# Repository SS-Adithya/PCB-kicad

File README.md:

# PCB-kicad

This is a repositary made to put all my Kicad works and there will be some good projects done here.

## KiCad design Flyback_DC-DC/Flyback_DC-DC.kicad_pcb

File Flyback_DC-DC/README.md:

This a PCB design for a 5V DC-DC Flyback converter that is not exacty the most optimised but on a working level.

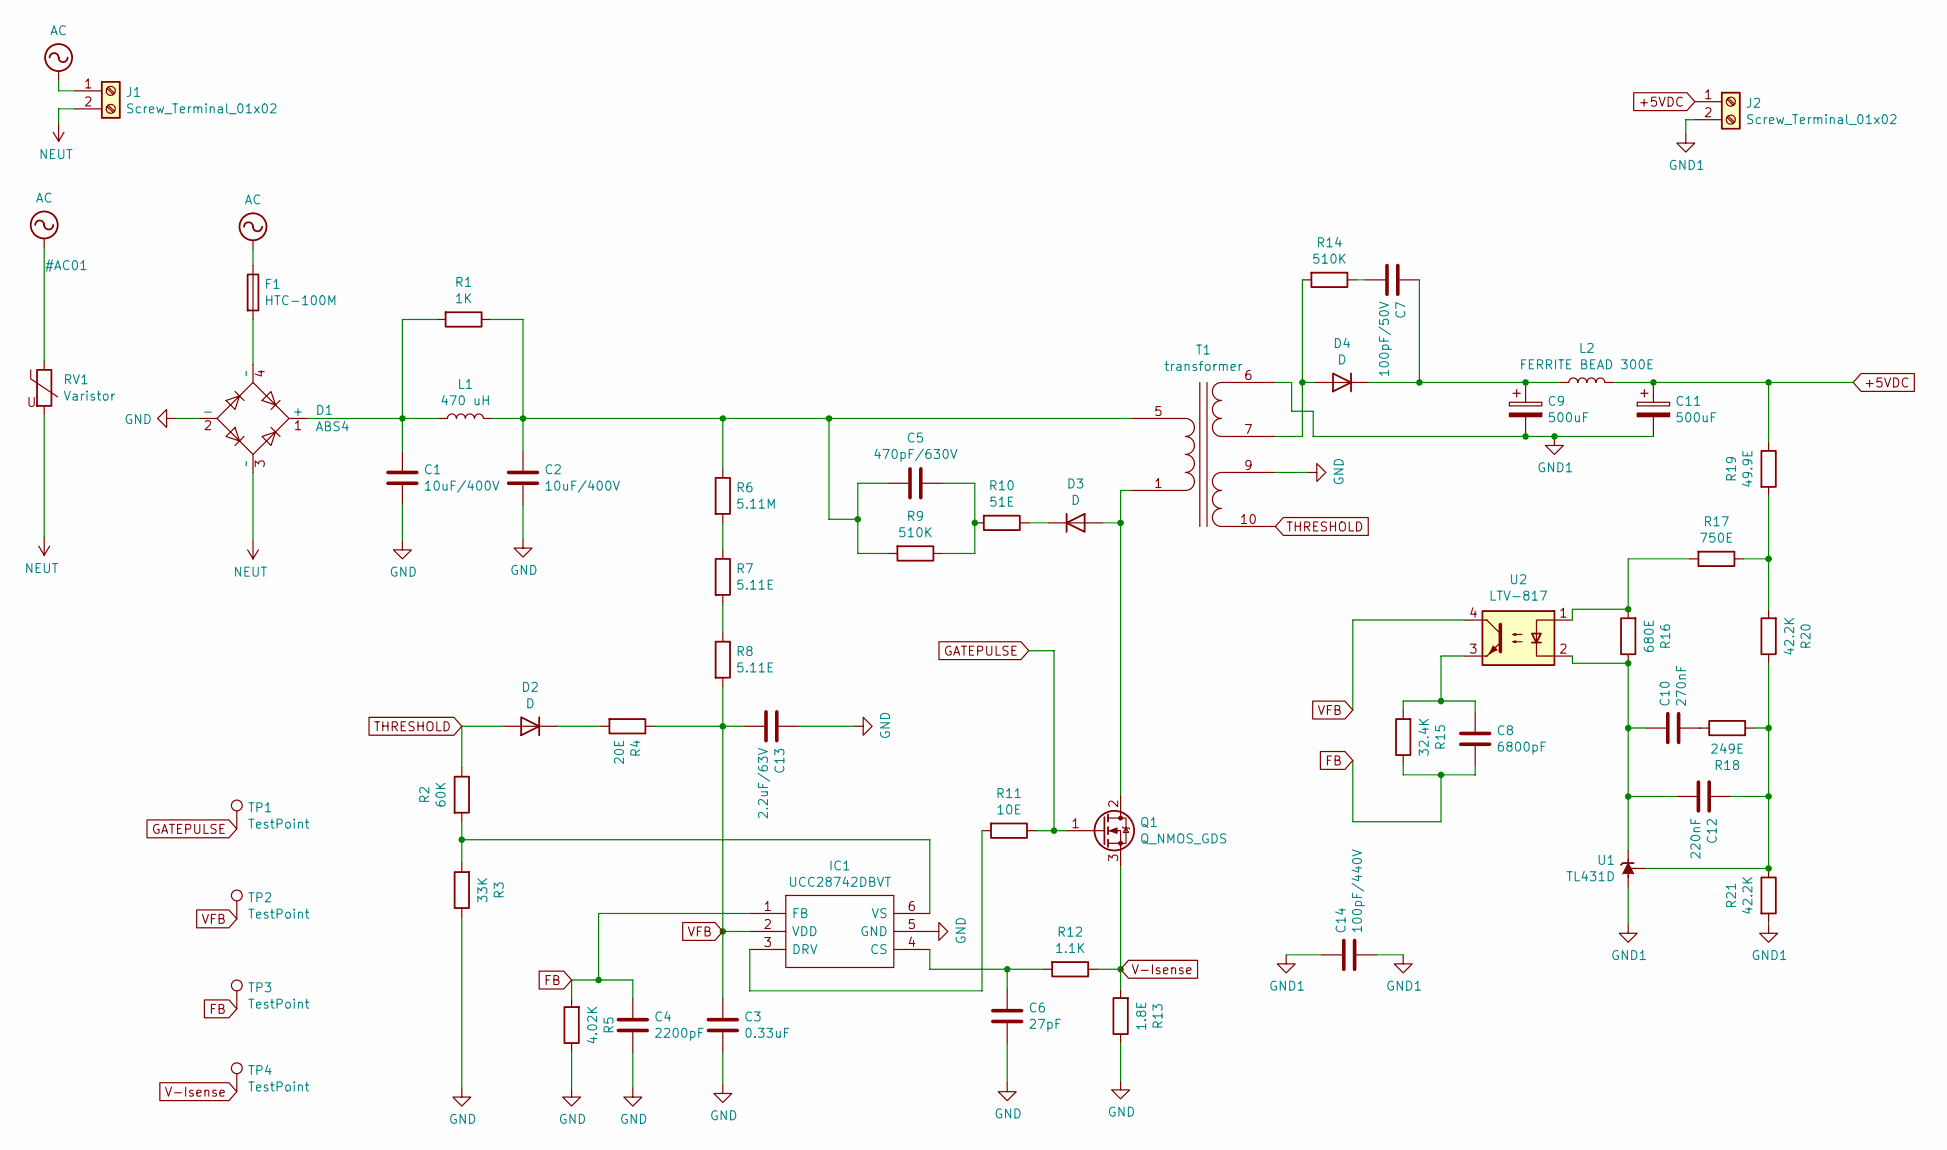
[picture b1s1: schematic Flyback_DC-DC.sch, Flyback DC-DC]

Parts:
C1, C2: 10uF/400V; CP_Radial_D10.0mm_P5.00mm
C3: 0.33uF; C_0805_2012Metric_Pad1.18x1.45mm_HandSolder
C4: 2200pF; C_0805_2012Metric_Pad1.18x1.45mm_HandSolder
C5: 470pF/630V; C_1206_3216Metric
C6: 27pF; C_0805_2012Metric_Pad1.18x1.45mm_HandSolder
C7: 100pF/50V; C_0201_0603Metric_Pad0.64x0.40mm_HandSolder
C8: 6800pF; C_0805_2012Metric_Pad1.18x1.45mm_HandSolder
C9, C11: 500uF; CP_Radial_D8.0mm_P3.50mm
C10: 270nF; C_0805_2012Metric_Pad1.18x1.45mm_HandSolder
C12: 220nF; C_0805_2012Metric_Pad1.18x1.45mm_HandSolder
C13: 2.2uF/63V; CP_Radial_D8.0mm_P3.50mm
C14: 100pF/440V; C_Disc_D10.5mm_W5.0mm_P7.50mm
D1: ABS4; Diode_Bridge_Diotec_ABS
D2, D3, D4: D; D_1206_3216Metric_Castellated
F1: HTC-100M; HTC100M
IC1: UCC28742DBVT; SOT95P280X145-6N; Manufacturer_Part_Number UCC28742DBVT; Mouser Part Number 595-UCC28742DBVT
J1: Screw_Terminal_01x02; TerminalBlock_bornier-3_P5.08mm
J2: Screw_Terminal_01x02; TerminalBlock_bornier-2_P5.08mm
L1: 470 uH; RLB0914
L2: FERRITE BEAD 300E; L_0805_2012Metric_Pad1.05x1.20mm_HandSolder
Q1: Q_NMOS_GDS; TO-252-2
R1: 1K; R_0805_2012Metric_Pad1.20x1.40mm_HandSolder
R2: 60K; R_0805_2012Metric_Pad1.20x1.40mm_HandSolder
R3: 33K; R_0805_2012Metric_Pad1.20x1.40mm_HandSolder
R4: 20E; R_0805_2012Metric_Pad1.20x1.40mm_HandSolder
R5: 4.02K; R_0805_2012Metric_Pad1.20x1.40mm_HandSolder
R6: 5.11M; R_1206_3216Metric
R7, R8: 5.11E; R_1206_3216Metric
R9, R14: 510K; R_0805_2012Metric_Pad1.20x1.40mm_HandSolder
R10: 51E; R_0805_2012Metric_Pad1.20x1.40mm_HandSolder
R11: 10E; R_0805_2012Metric_Pad1.20x1.40mm_HandSolder
R12: 1.1K; R_0805_2012Metric_Pad1.20x1.40mm_HandSolder
R13: 1.8E; R_0805_2012Metric_Pad1.20x1.40mm_HandSolder
R15: 32.4K; R_0805_2012Metric_Pad1.20x1.40mm_HandSolder
R16: 680E; R_0805_2012Metric_Pad1.20x1.40mm_HandSolder
R17: 750E; R_0805_2012Metric_Pad1.20x1.40mm_HandSolder
R18: 249E; R_0805_2012Metric_Pad1.20x1.40mm_HandSolder
R19: 49.9E; R_0805_2012Metric_Pad1.20x1.40mm_HandSolder
R20, R21: 42.2K; R_0805_2012Metric_Pad1.20x1.40mm_HandSolder
RV1: Varistor; MOV14D431KTR
T1: transformer; Transformer_CHK_EI42-5VA_2xSec
TP1, TP2, TP3, TP4: TestPoint; PinHeader_1x01_P2.54mm_Vertical
U1: TL431D; SOIC-8_3.9x4.9mm_P1.27mm
U2: LTV-817; DIP-4_W7.62mm

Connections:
+5VDC: C11.1, J2.1, L2.2, R19.1
AC: F1.1, J1.1, RV1.1
FB: C4.1, C8.2, IC1.1 (FB), R5.2, R15.1, TP3.1
GATEPULSE: Q1.1 (G), R11.1, TP1.1
GND: C1.2, C2.2, C3.2, C4.2, C6.2, C13.1, D1.2 (-), IC1.5 (GND), R3.1, R5.1, R13.1, T1.9 (SC)
GND1: C9.2, C11.2, C14.1, C14.2, J2.2, R21.2, T1.6 (SA), U1.2 (A), U1.3 (A), U1.6 (A), U1.7 (A)
NEUT: D1.3 (~~), J1.2, RV1.2
unnamed: C1.1, D1.1 (+), L1.1, R1.2
unnamed: C2.1, C5.2, L1.2, R1.1, R6.1, R9.2, T1.5 (AA)
unnamed: C5.1, R9.1, R10.2
unnamed: C6.1, IC1.4 (CS), R12.2
unnamed: C7.1, C9.1, D4.1 (K), L2.1
unnamed: C7.2, R14.1
unnamed: C8.1, R15.2, U2.3
unnamed: C10.1, C12.2, R16.1, U1.1 (K), U2.2
unnamed: C10.2, R18.1
unnamed: C12.1, R18.2, R20.1, R21.1, U1.8 (REF)
unnamed: D1.4 (~~), F1.2
unnamed: D2.1 (K), R4.2
unnamed: D3.1 (K), R10.1
unnamed: D3.2 (A), Q1.2 (D), T1.1 (AB)
unnamed: D4.2 (A), R14.2, T1.7 (SB)
unnamed: IC1.3 (DRV), R11.2
unnamed: IC1.6 (VS), R2.2, R3.2
unnamed: R6.2, R7.1
unnamed: R7.2, R8.1
unnamed: R16.2, R17.2, U2.1
unnamed: R17.1, R19.2, R20.2
THRESHOLD: D2.2 (A), R2.1, T1.10 (SD)
V-Isense: Q1.3 (S), R12.1, R13.2, TP4.1
VFB: C3.1, C13.2, IC1.2 (VDD), R4.1, R8.2, TP2.1, U2.4

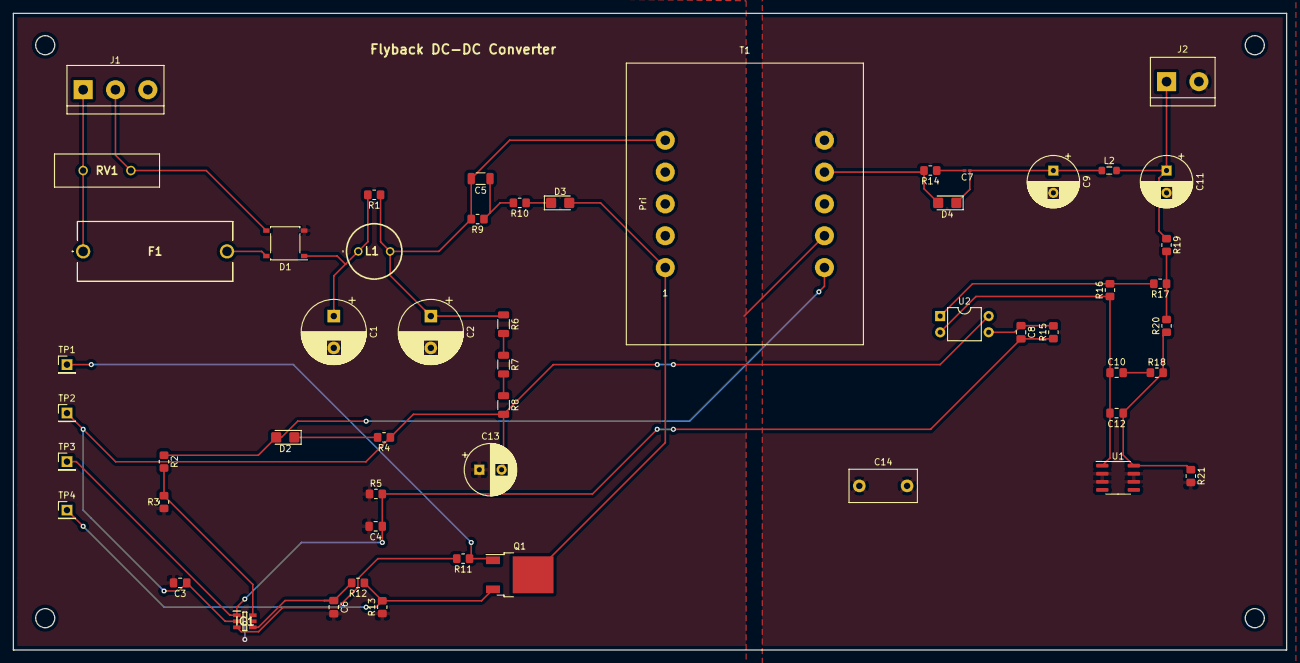
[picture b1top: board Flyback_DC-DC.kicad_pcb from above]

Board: 2 copper layers, 200.0 x 100.0 mm, 54 parts (0 on the bottom side), 31 nets.

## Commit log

2024-07-26 Create LICENSE
